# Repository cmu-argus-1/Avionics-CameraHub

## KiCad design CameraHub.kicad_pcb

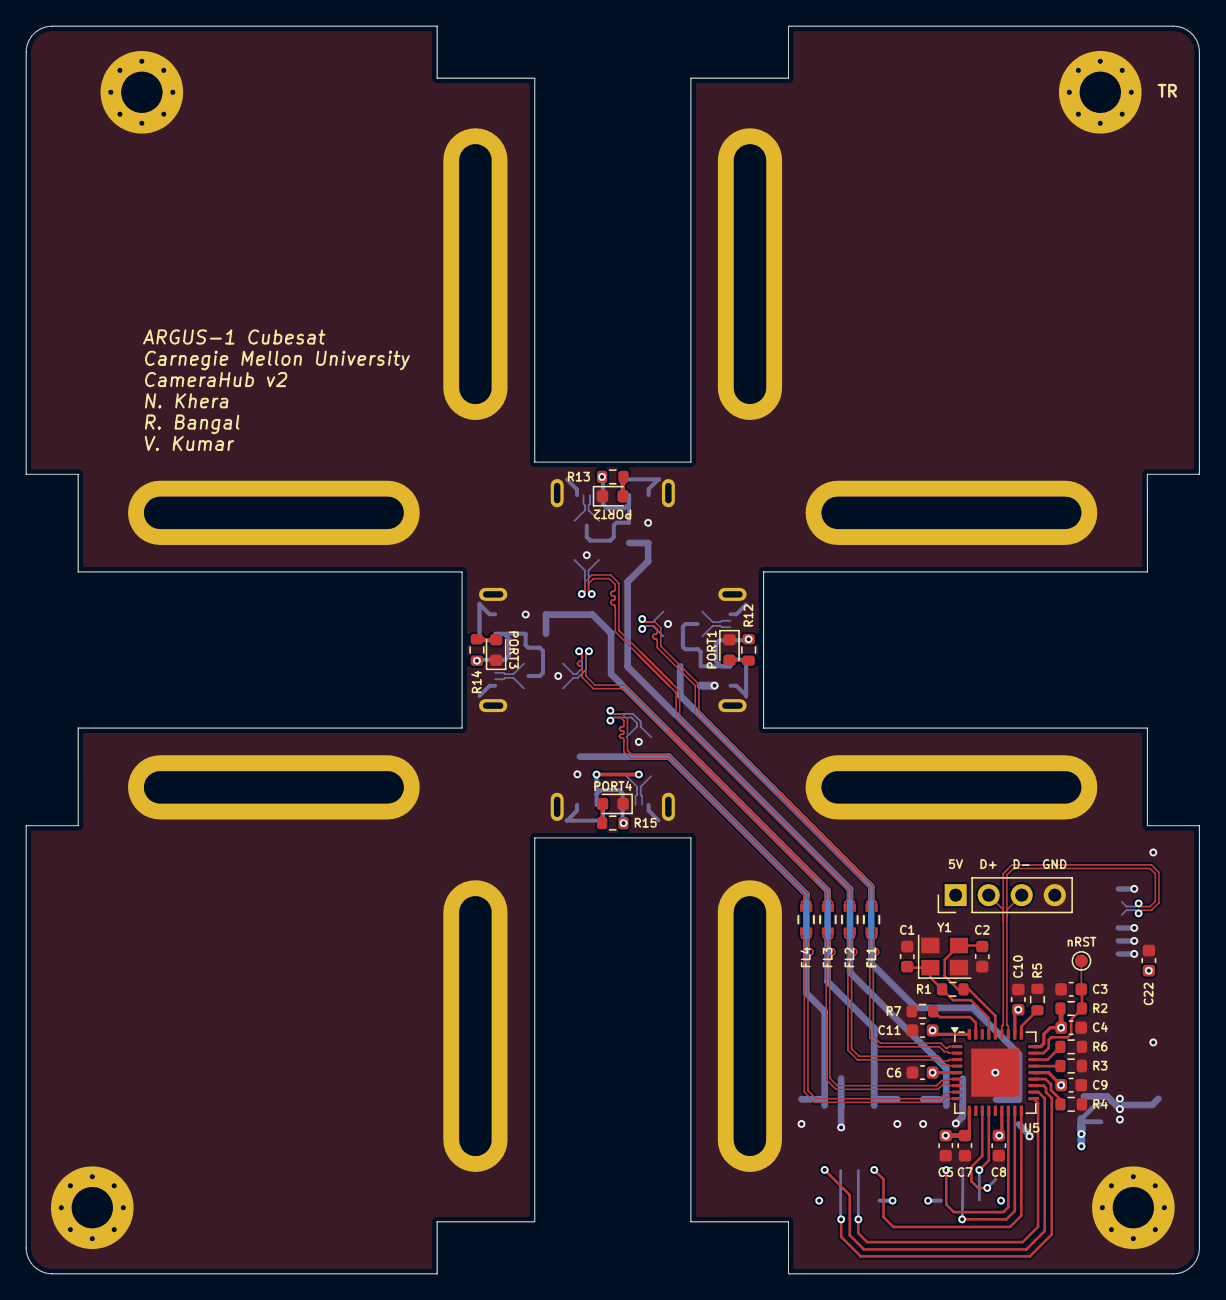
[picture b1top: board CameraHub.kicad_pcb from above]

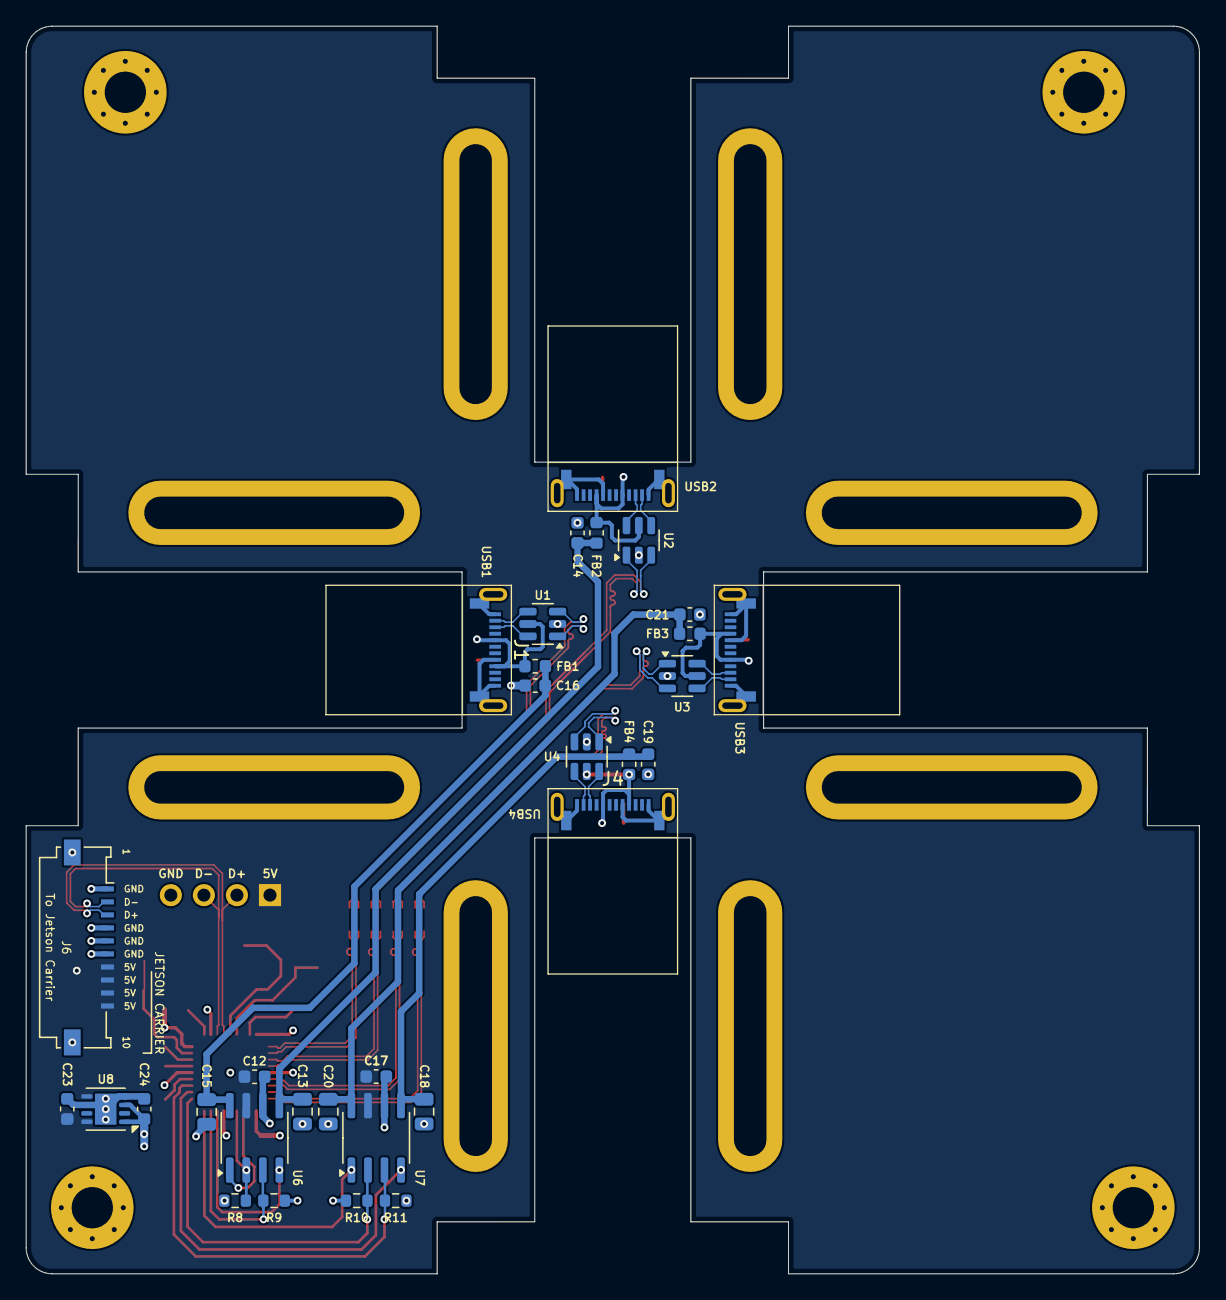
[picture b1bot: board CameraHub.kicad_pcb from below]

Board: 4 copper layers, 90.2 x 95.9 mm, 79 parts (36 on the bottom side), 57 nets.

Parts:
C1, C2: 27pF; C_0603_1608Metric
C3, C6, C7, C8, C9, C10, C11, C12, C14, C16, C17, C19, C21: 0.1uF; C_0603_1608Metric
C4: 4.7uF; C_0603_1608Metric
C5, C22, C23: 1uF; C_0603_1608Metric
C13, C15, C18, C20: 100uF; C_0805_2012Metric
C24: 22uF; C_0603_1608Metric
D1, D2, D3, D4: Green; LED_0603_1608Metric
FB1, FB2, FB3, FB4: 600R; L_0603_1608Metric
FL1, FL2, FL3, FL4: 744230900; CHIP_230900_WRE
H1, H2, H3, H4: MountingHole_Pad; MountingHole2
H5, H6, H7, H8, H9, H10, H11, H12: MountingHole_Pad; MountingHole_USB
J1, J2, J3, J4: USB_C_Receptacle_USB2.0_16P; USBC-121SMT-4BS2S
J5: Header 01x04 0.1"; PinHeader_1x04_P2.54mm_Vertical
J6: 200528-0100; Molex_200528-0100_1x10-1MP_P1.00mm_Horizontal
R1: 1M; R_0603_1608Metric
R2: 100K; R_0603_1608Metric
R3, R4, R5, R6: 36K; R_0603_1608Metric
R7: 12K; R_0603_1608Metric
R8, R9, R10, R11: 10K; R_0603_1608Metric
R12, R13, R14, R15: 330R; R_0603_1608Metric
U1, U2, U3, U4: USBLC6-2P6; SOT-23-6
U5: USB2514B-I/M2; QFN-36-1EP_6x6mm_P0.5mm_EP3.7x3.7mm
U6, U7: MIC2026-1xM; SOIC-8_3.9x4.9mm_P1.27mm
U8: TLV76733QWDRBxQ1; VSON-8-1EP_3x3mm_P0.65mm_EP1.65x2.4mm
Y1: 24MHz; Crystal_SMD_3225-4Pin_3.2x2.5mm
nRST: Conn_01x01; TestPoint_Pad_D1.0mm

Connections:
+3.3V: C4.1, C5.1, C6.1, C7.1, C8.1, C9.1, C10.1, C11.1, C24.1, R2.2, R8.1, R9.1, R10.1, R11.1, U5.5 (VDDA33), U5.10 (VDDA33), U5.15 (VDD33), U5.23 (VDD33), U5.27 (VBUS_DET), U5.29 (VDDA33), U5.36 (VDDA33), U8.1 (OUT), U8.3 (SNS)
+5V: C12.1, C17.1, C22.2, C23.1, J5.1, J6.7, J6.8, J6.9, J6.10, U6.7 (IN), U7.7 (IN), U8.5 (EN), U8.8 (IN)
/Hub 2/D1_N: J1.A7 (D-), U1.4 (I/O2)
/Hub 2/D1_P: J1.A6 (D+), U1.6 (I/O1)
/Hub 2/D2_N: J2.A7 (D-), U2.4 (I/O2)
/Hub 2/D2_P: J2.A6 (D+), U2.6 (I/O1)
/Hub 2/D3_N: J3.A7 (D-), U3.4 (I/O2)
/Hub 2/D3_P: J3.A6 (D+), U3.6 (I/O1)
/Hub 2/D4_N: J4.A7 (D-), U4.4 (I/O2)
/Hub 2/D4_P: J4.A6 (D+), U4.6 (I/O1)
/Hub 2/FD1_N: FL1.3, U1.3 (I/O2)
/Hub 2/FD1_P: FL1.2, U1.1 (I/O1)
/Hub 2/FD2_N: FL2.3, U2.3 (I/O2)
/Hub 2/FD2_P: FL2.2, U2.1 (I/O1)
/Hub 2/FD3_N: FL3.3, U3.3 (I/O2)
/Hub 2/FD3_P: FL3.2, U3.1 (I/O1)
/Hub 2/FD4_N: FL4.3, U4.3 (I/O2)
/Hub 2/FD4_P: FL4.2, U4.1 (I/O1)
/Hub 2/HD1_N: FL1.4, U5.1 (USBDM_DN1/PRT_DIS_M1)
/Hub 2/HD1_P: FL1.1, U5.2 (USBDP_DN1/PRT_DIS_P1)
/Hub 2/HD2_N: FL2.4, U5.3 (USBDM_DN2/PRT_DIS_M2)
/Hub 2/HD2_P: FL2.1, U5.4 (USBDP_DN2/PRT_DIS_P2)
/Hub 2/HD3_N: FL3.4, U5.6 (USBDM_DN3/PRT_DIS_M3)
/Hub 2/HD3_P: FL3.1, U5.7 (USBDP_DN3/PRT_DIS_P3)
/Hub 2/HD4_N: FL4.4, U5.8 (USBDM_DN4/PRT_DIS_M4)
/Hub 2/HD4_P: FL4.1, U5.9 (USBDP_DN4/PRT_DIS_P4)
/Hub 2/PWR1: U5.12 (PRTPWR1/BC_EN1), U6.1 (ENA)
/Hub 2/PWR2: U5.16 (PRTPWR2/BC_EN2), U6.4 (ENB)
/Hub 2/PWR3: U5.18 (PRTPWR3/BC_EN3), U7.1 (ENA)
/Hub 2/PWR4: U5.20 (PRTPWR4/BC_EN4), U7.4 (ENB)
/Hub 2/VBUS1: C15.1, C16.1, FB1.1, U6.8 (OUTA)
/Hub 2/VBUS2: C13.1, C14.1, FB2.1, U6.5 (OUTB)
/Hub 2/VBUS3: C20.1, C21.1, FB3.1, U7.8 (OUTA)
/Hub 2/VBUS4: C18.1, C19.1, FB4.1, U7.5 (OUTB)
/Hub 2/VBUS_CONN1: FB1.2, J1.A4 (VBUS), J1.B9 (VBUS), R12.1, U1.5 (VBUS)
/Hub 2/VBUS_CONN2: FB2.2, J2.A4 (VBUS), J2.B9 (VBUS), R13.1, U2.5 (VBUS)
/Hub 2/VBUS_CONN3: FB3.2, J3.A4 (VBUS), J3.B9 (VBUS), R14.1, U3.5 (VBUS)
/Hub 2/VBUS_CONN4: FB4.2, J4.A4 (VBUS), J4.B9 (VBUS), R15.1, U4.5 (VBUS)
/Hub 2/nOCS1: R8.2, U5.13 (OCS_N1), U6.2 (FLGA)
/Hub 2/nOCS2: R9.2, U5.17 (OCS_N2), U6.3 (FLGB)
/Hub 2/nOCS3: R10.2, U5.19 (OCS_N3), U7.2 (FLGA)
/Hub 2/nOCS4: R11.2, U5.21 (OCS_N4), U7.3 (FLGB)
/USB_N: J5.3, J6.2, U5.30 (USBDM_UP)
/USB_P: J5.2, J6.3, U5.31 (USBDP_UP)
/nRST: C3.1, R2.1, U5.26 (RESET_N), nRST.1
GND: C1.2, C2.2, C3.2, C4.2, C5.2, C6.2, C7.2, C8.2, C9.2, C10.2, C11.2, C12.2, C13.2, C14.2, C15.2, C16.2, C17.2, C18.2, C19.2, C20.2, C21.2, C22.1, C23.2, C24.2, D1.1 (K), D2.1 (K), D3.1 (K), D4.1 (K), H1.1, H2.1, H3.1, H4.1, H5.1, H6.1, H7.1, H8.1, H9.1, H10.1, H11.1, H12.1, J1.A1 (GND), J1.A12 (GND), J1.B12 (GND), J1.S1 (SHIELD), J2.A1 (GND), J2.A12 (GND), J2.B12 (GND), J2.S1 (SHIELD), J3.A1 (GND), J3.A12 (GND), J3.B12 (GND), J3.S1 (SHIELD), J4.A1 (GND), J4.A12 (GND), J4.B12 (GND), J4.S1 (SHIELD), J5.4, J6.1, J6.4, J6.5, J6.6, J6.MP (MountPin), R3.2, R4.2, R5.2, R6.2, R7.1, U1.2 (GND), U2.2 (GND), U3.2 (GND), U4.2 (GND), U5.37 (VSS), U6.6 (GND), U7.6 (GND), U8.4 (GND), U8.6 (GND), U8.9 (PAD), Y1.2, Y1.4
unnamed: D1.2 (A), R12.2
unnamed: D2.2 (A), R13.2
unnamed: D3.2 (A), R14.2
unnamed: D4.2 (A), R15.2
unnamed: R6.1, U5.25 (HS_IND/CFG_SEL1)
unnamed: R7.2, U5.35 (RBIAS)
unnamed: R3.1, U5.24 (SCL/SMBCLK/CFG_SEL0)
unnamed: R4.1, U5.22 (SDA/SMBDATA/NON_REM1)
unnamed: R5.1, U5.28 (SUSP_IND/LOCAL_PWR/NON_REM0)
unnamed: C1.1, R1.1, U5.33 (XTALIN/CLKIN), Y1.1
unnamed: C2.1, R1.2, U5.32 (XTALOUT), Y1.3

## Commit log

2024-11-19 Updated for single USB line

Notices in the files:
parts and their libraries:
License: Apache-2.0
